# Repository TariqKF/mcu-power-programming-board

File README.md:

# Embedded MCU Power & Programming Board

Custom ESP32-S3 development board designed in KiCad.

- **MCU:** ESP32-S3-WROOM-1 module
- **USB-C:** USB 2.0 receptacle for power and programming
- **ESD protection:** USBLC6-2SC6 on the USB data lines
- **Regulation:** AMS1117-3.3 regulator with bulk and decoupling capacitors
- **Controls:** two push buttons
- **Expansion:** 2x 20-pin headers

## Files

- `Micro-Controller-V1.kicad_sch`: schematic
- `Micro-Controller-V1.kicad_pcb`: PCB layout
- `MY_Footprints.pretty/`: custom ESP32-S3-WROOM-1 footprint

Open `Micro-Controller-V1.kicad_pro` in KiCad 10.

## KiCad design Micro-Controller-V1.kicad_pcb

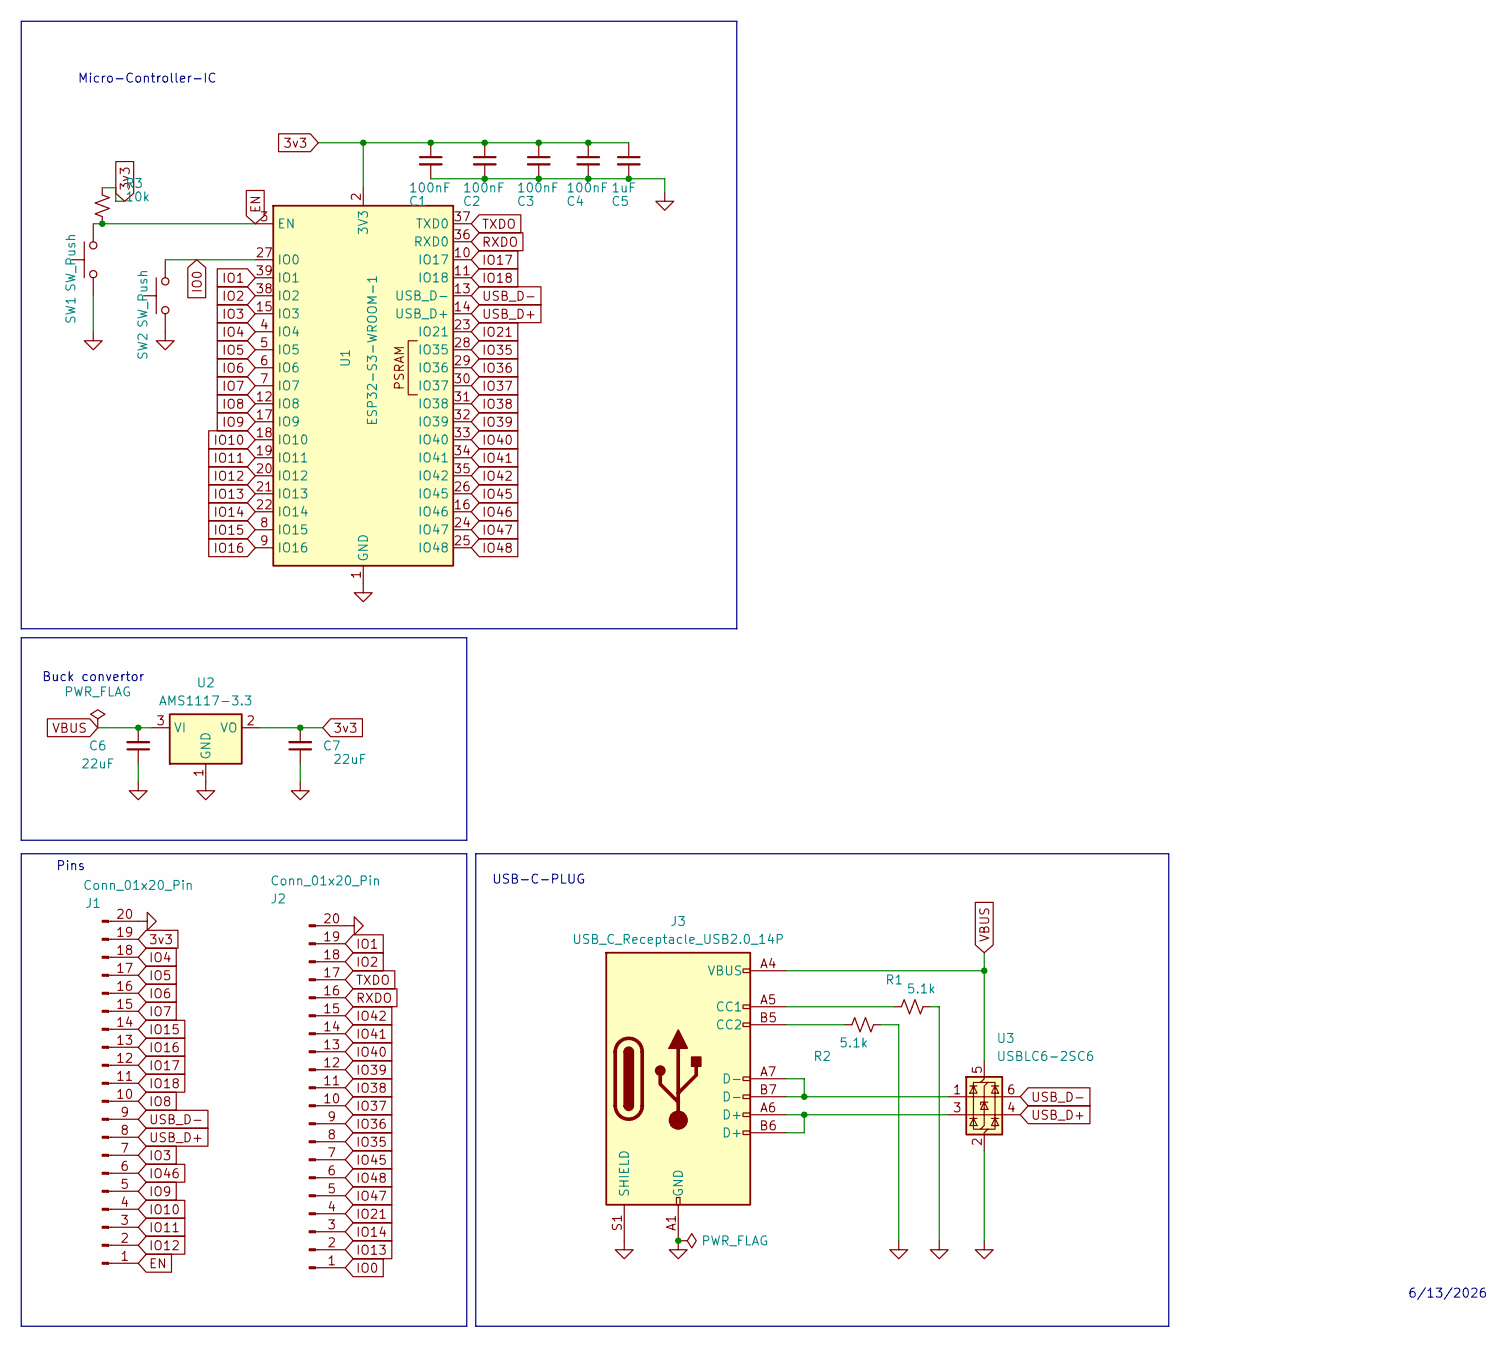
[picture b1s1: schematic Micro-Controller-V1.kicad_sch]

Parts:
C1, C2, C3, C4: 100nF; C_1206_3216Metric_Pad1.33x1.80mm_HandSolder
C5: 1uF; C_1206_3216Metric_Pad1.33x1.80mm_HandSolder
C6, C7: 22uF; C_1206_3216Metric_Pad1.33x1.80mm_HandSolder
J1, J2: Conn_01x20_Pin; PinHeader_1x20_P2.54mm_Vertical
J3: USB_C_Receptacle_USB2.0_14P; USB_C_Receptacle_HRO_TYPE-C-31-M-12
R1, R2: 5.1k; R_0805_2012Metric_Pad1.20x1.40mm_HandSolder
R3: 10k; R_0805_2012Metric_Pad1.20x1.40mm_HandSolder
SW1, SW2: SW_Push; SW_Push_1P1T_NO_CK_KMR2
U1: ESP32-S3-WROOM-1
U2: AMS1117-3.3; SOT-223-3_TabPin2
U3: USBLC6-2SC6; SOT-23-6

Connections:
3v3: C1.1, C2.1, C3.1, C4.1, C5.1, C7.2, J1.19, R3.1, U1.2 (3V3), U2.2 (VO)
EN: J1.1, R3.2, SW1.2, U1.3 (EN)
GND: C1.2, C2.2, C3.2, C4.2, C5.2, C6.1, C7.1, J1.20, J2.20, J3.A1 (GND), J3.A12 (GND), J3.B1 (GND), J3.B12 (GND), J3.S1 (SHIELD), R1.1, R2.2, SW1.1, SW2.1, U1.1 (GND), U1.40 (GND), U1.41 (GND), U2.1 (GND), U3.2 (GND)
IO0: J2.1, SW2.2, U1.27 (IO0)
IO1: J2.19, U1.39 (IO1)
IO2: J2.18, U1.38 (IO2)
IO3: J1.7, U1.15 (IO3)
IO4: J1.18, U1.4 (IO4)
IO5: J1.17, U1.5 (IO5)
IO6: J1.16, U1.6 (IO6)
IO7: J1.15, U1.7 (IO7)
IO8: J1.10, U1.12 (IO8)
IO9: J1.5, U1.17 (IO9)
IO10: J1.4, U1.18 (IO10)
IO11: J1.3, U1.19 (IO11)
IO12: J1.2, U1.20 (IO12)
IO13: J2.2, U1.21 (IO13)
IO14: J2.3, U1.22 (IO14)
IO15: J1.14, U1.8 (IO15)
IO16: J1.13, U1.9 (IO16)
IO17: J1.12, U1.10 (IO17)
IO18: J1.11, U1.11 (IO18)
IO21: J2.4, U1.23 (IO21)
IO35: J2.8, U1.28 (IO35)
IO36: J2.9, U1.29 (IO36)
IO37: J2.10, U1.30 (IO37)
IO38: J2.11, U1.31 (IO38)
IO39: J2.12, U1.32 (IO39)
IO40: J2.13, U1.33 (IO40)
IO41: J2.14, U1.34 (IO41)
IO42: J2.15, U1.35 (IO42)
IO45: J2.7, U1.26 (IO45)
IO46: J1.6, U1.16 (IO46)
IO47: J2.5, U1.24 (IO47)
IO48: J2.6, U1.25 (IO48)
unnamed: J3.A5 (CC1), R1.2
unnamed: J3.B5 (CC2), R2.1
unnamed: J3.A6 (D+), J3.B6 (D+), U3.3 (I/O2)
unnamed: J3.A7 (D-), J3.B7 (D-), U3.1 (I/O1)
RXDO: J2.16, U1.36 (RXD0)
TXDO: J2.17, U1.37 (TXD0)
USB_D+: J1.8, U1.14 (USB_D+), U3.4 (I/O2)
USB_D-: J1.9, U1.13 (USB_D-), U3.6 (I/O1)
VBUS: C6.2, J3.A4 (VBUS), J3.A9 (VBUS), J3.B4 (VBUS), J3.B9 (VBUS), U2.3 (VI), U3.5 (VBUS)

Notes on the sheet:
Pins
6/13/2026
Micro-Controller-IC
USB-C-PLUG
Buck convertor

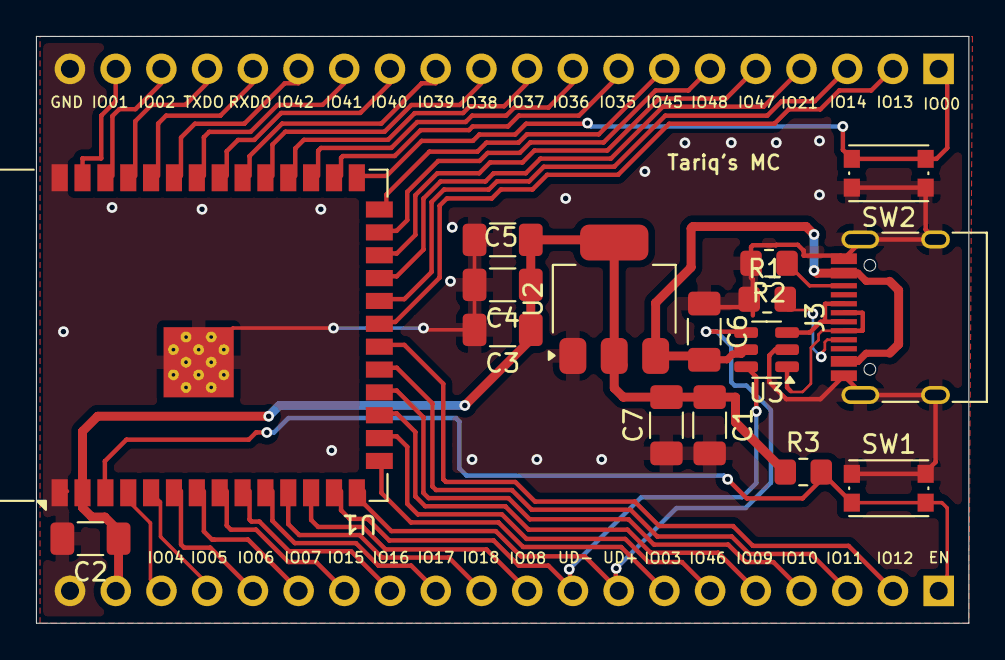
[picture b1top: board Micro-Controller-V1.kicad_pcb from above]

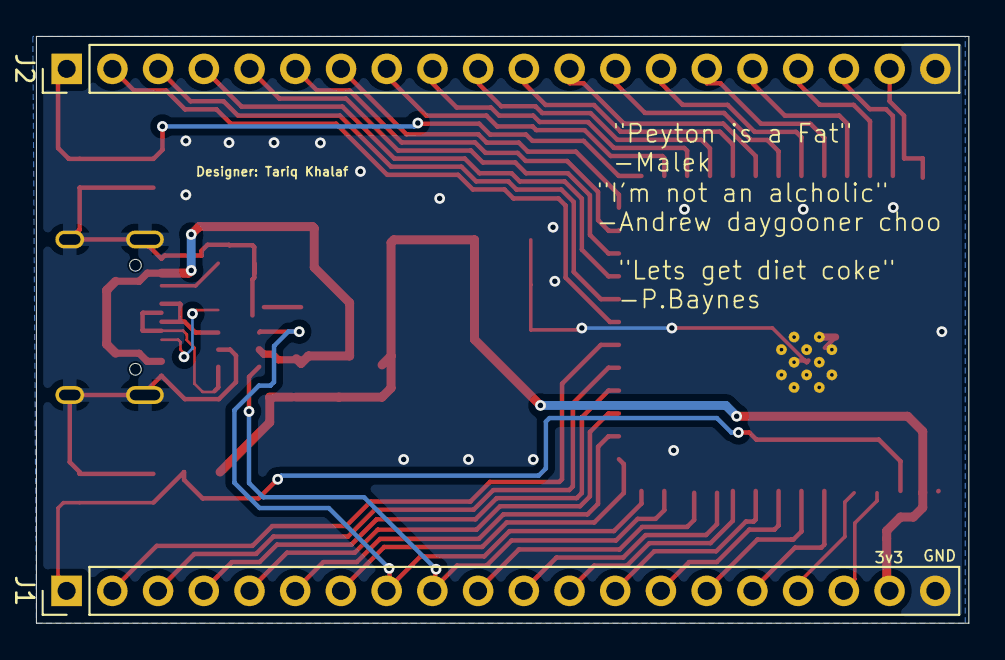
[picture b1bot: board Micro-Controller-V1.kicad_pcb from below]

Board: 2 copper layers, 51.8 x 32.6 mm, 18 parts (2 on the bottom side), 44 nets.
